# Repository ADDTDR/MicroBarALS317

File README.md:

# ALS317 Bar graph display
## Based on is31fl3730 i2c led driver and ALS317 5 segment led display

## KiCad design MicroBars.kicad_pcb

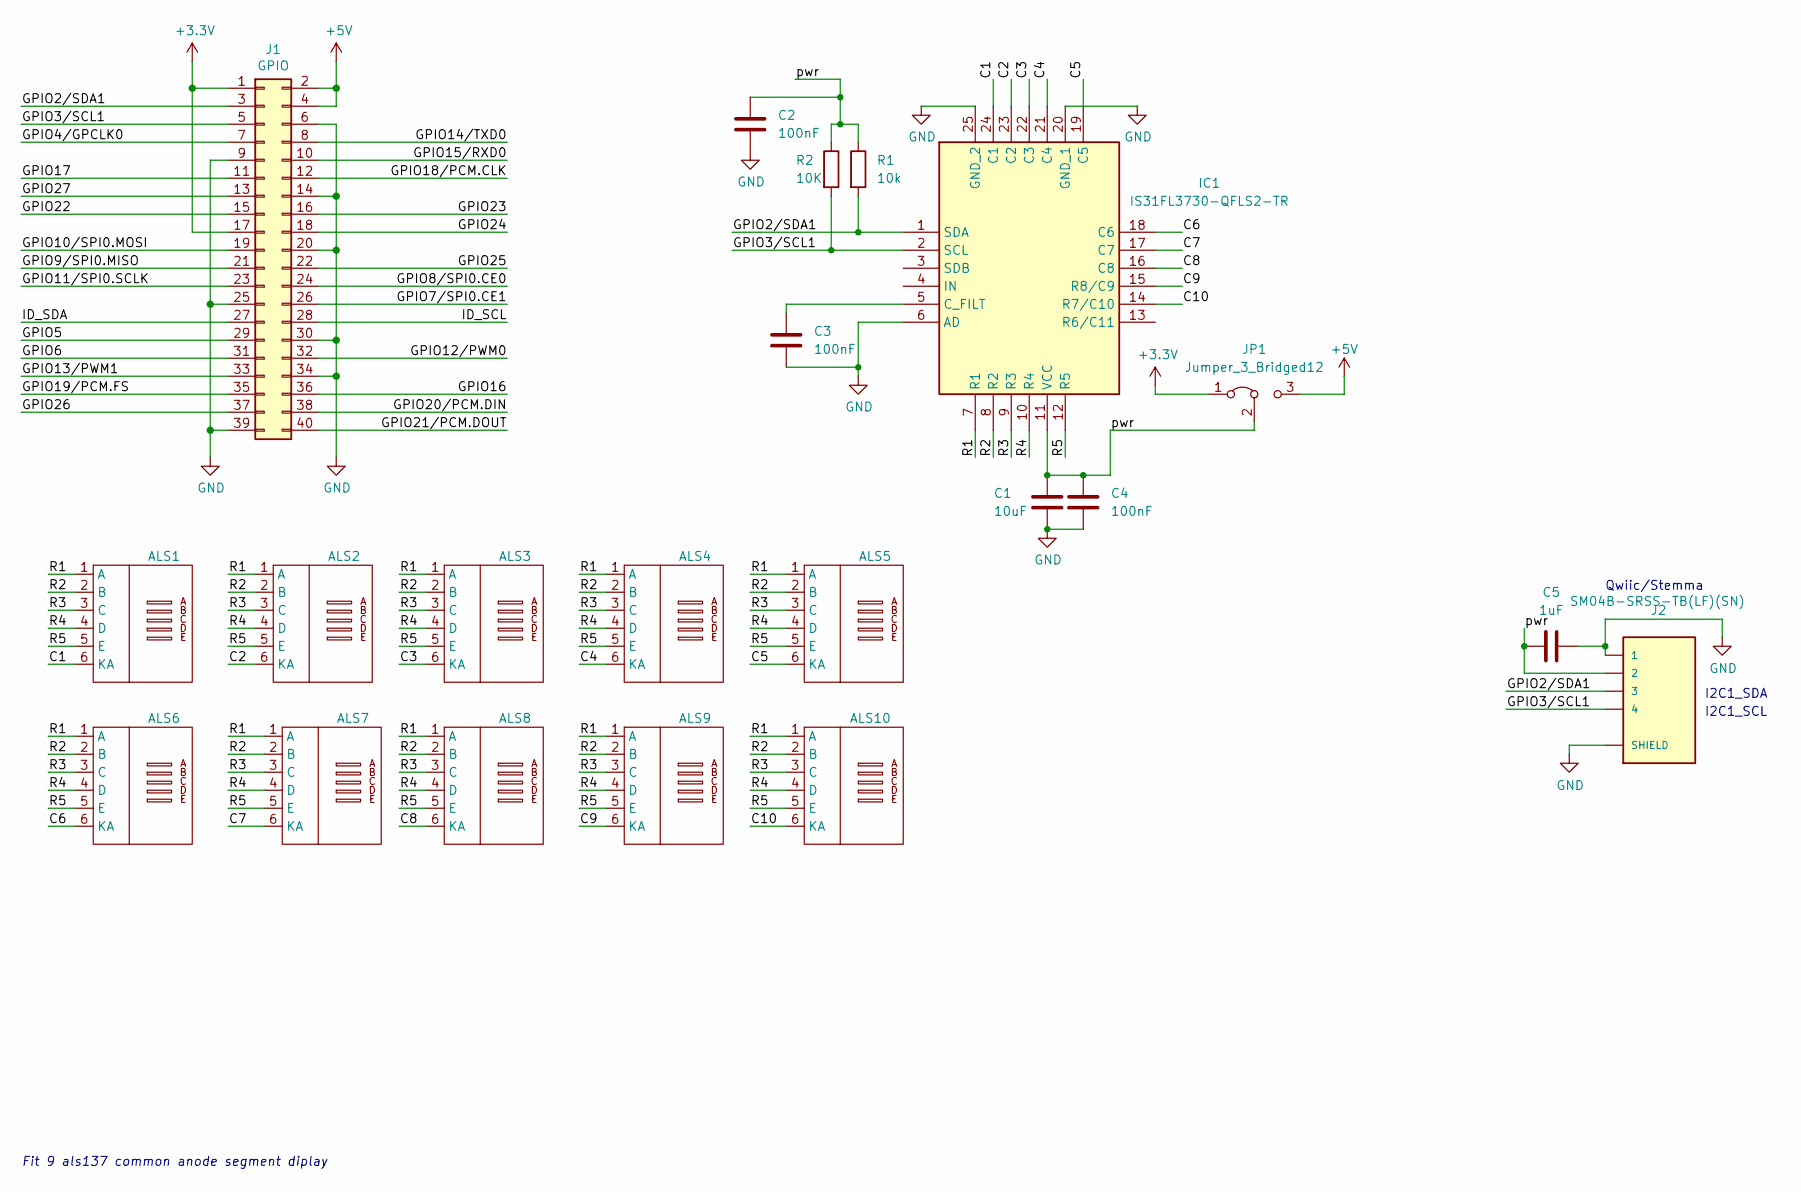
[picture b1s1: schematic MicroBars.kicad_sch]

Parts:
ALS1, ALS2, ALS3, ALS4, ALS5, ALS6, ALS7, ALS8, ALS9, ALS10: als317
C1: 10uF; C_0805_2012Metric
C2, C3, C4: 100nF; C_0603_1608Metric_Pad1.08x0.95mm_HandSolder
C5: 1uF; C_1210_3225Metric_Pad1.33x2.70mm_HandSolder
IC1: IS31FL3730-QFLS2-TR; QFN50P400X400X80-25N-D; Manufacturer_Part_Number IS31FL3730-QFLS2-TR; Mouser Part Number 870-IS31FL3730QFLS2R
J1: GPIO; PinSocket_2x20_P2.54mm_Vertical
J2: SM04B-SRSS-TB(LF)(SN); JST_SM04B-SRSS-TB(LF)(SN); MPN SM04B-SRSS-TB(LF)(SN); Digi-Key_PN 455-1804-1-ND
JP1: Jumper_3_Bridged12; SolderJumper-3_P1.3mm_Bridged12_Pad1.0x1.5mm
R1: 10k; R_0603_1608Metric_Pad0.98x0.95mm_HandSolder
R2: 10K; R_0603_1608Metric_Pad0.98x0.95mm_HandSolder

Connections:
+3V3: J1.1, J1.17, JP1.1 (A); also elsewhere on the board
+5V: J1.2, J1.4, JP1.3 (B); also elsewhere on the board
/C1: ALS1.6 (KA), IC1.24 (C1)
/C2: ALS2.6 (KA), IC1.23 (C2)
/C3: ALS3.6 (KA), IC1.22 (C3)
/C4: ALS4.6 (KA), IC1.21 (C4)
/C5: ALS5.6 (KA), IC1.19 (C5)
/C6: ALS6.6 (KA), IC1.18 (C6)
/C7: ALS7.6 (KA), IC1.17 (C7)
/C8: ALS8.6 (KA), IC1.16 (C8)
/C9: ALS9.6 (KA), IC1.15 (R8/C9)
/C10: ALS10.6 (KA), IC1.14 (R7/C10)
/GPIO2/SDA1: IC1.1 (SDA), J1.3, J2.3, R1.2
/GPIO3/SCL1: IC1.2 (SCL), J1.5, J2.4, R2.2
/GPIO4/GPCLK0: J1.7
/GPIO5: J1.29
/GPIO6: J1.31
/GPIO7/SPI0.CE1: J1.26
/GPIO8/SPI0.CE0: J1.24
/GPIO9/SPI0.MISO: J1.21
/GPIO10/SPI0.MOSI: J1.19
/GPIO11/SPI0.SCLK: J1.23
/GPIO12/PWM0: J1.32
/GPIO13/PWM1: J1.33
/GPIO14/TXD0: J1.8
/GPIO15/RXD0: J1.10
/GPIO16: J1.36
/GPIO17: J1.11
/GPIO18/PCM.CLK: J1.12
/GPIO19/PCM.FS: J1.35
/GPIO20/PCM.DIN: J1.38
/GPIO21/PCM.DOUT: J1.40
/GPIO22: J1.15
/GPIO23: J1.16
/GPIO24: J1.18
/GPIO25: J1.22
/GPIO26: J1.37
/GPIO27: J1.13
/ID_SCL: J1.28
/ID_SDA: J1.27
/R1: ALS1.1 (A), ALS2.1 (A), ALS3.1 (A), ALS4.1 (A), ALS5.1 (A), ALS6.1 (A), ALS7.1 (A), ALS8.1 (A), ALS9.1 (A), ALS10.1 (A), IC1.7 (R1)
/R2: ALS1.2 (B), ALS2.2 (B), ALS3.2 (B), ALS4.2 (B), ALS5.2 (B), ALS6.2 (B), ALS7.2 (B), ALS8.2 (B), ALS9.2 (B), ALS10.2 (B), IC1.8 (R2)
/R3: ALS1.3 (C), ALS2.3 (C), ALS3.3 (C), ALS4.3 (C), ALS5.3 (C), ALS6.3 (C), ALS7.3 (C), ALS8.3 (C), ALS9.3 (C), ALS10.3 (C), IC1.9 (R3)
/R4: ALS1.4 (D), ALS2.4 (D), ALS3.4 (D), ALS4.4 (D), ALS5.4 (D), ALS6.4 (D), ALS7.4 (D), ALS8.4 (D), ALS9.4 (D), ALS10.4 (D), IC1.10 (R4)
/R5: ALS1.5 (E), ALS2.5 (E), ALS3.5 (E), ALS4.5 (E), ALS5.5 (E), ALS6.5 (E), ALS7.5 (E), ALS8.5 (E), ALS9.5 (E), ALS10.5 (E), IC1.12 (R5)
/pwr: C1.1, C2.1, C4.1, C5.1, IC1.11 (VCC), J2.2, R1.1, R2.1; also elsewhere on the board
GND: C1.2, C2.2, C3.2, C4.2, C5.2, IC1.6 (AD), IC1.20 (GND_1), IC1.25 (GND_2), J1.6, J1.9, J1.14, J1.20, J1.25, J1.30, J1.34, J1.39, J2.1, J2.S1 (SHIELD), J2.S2 (SHIELD)
unnamed: C3.1, IC1.5 (C_FILT)

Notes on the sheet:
Qwiic/Stemma
I2C1_SCL
Fit 9 als137 common anode segment diplay
I2C1_SDA

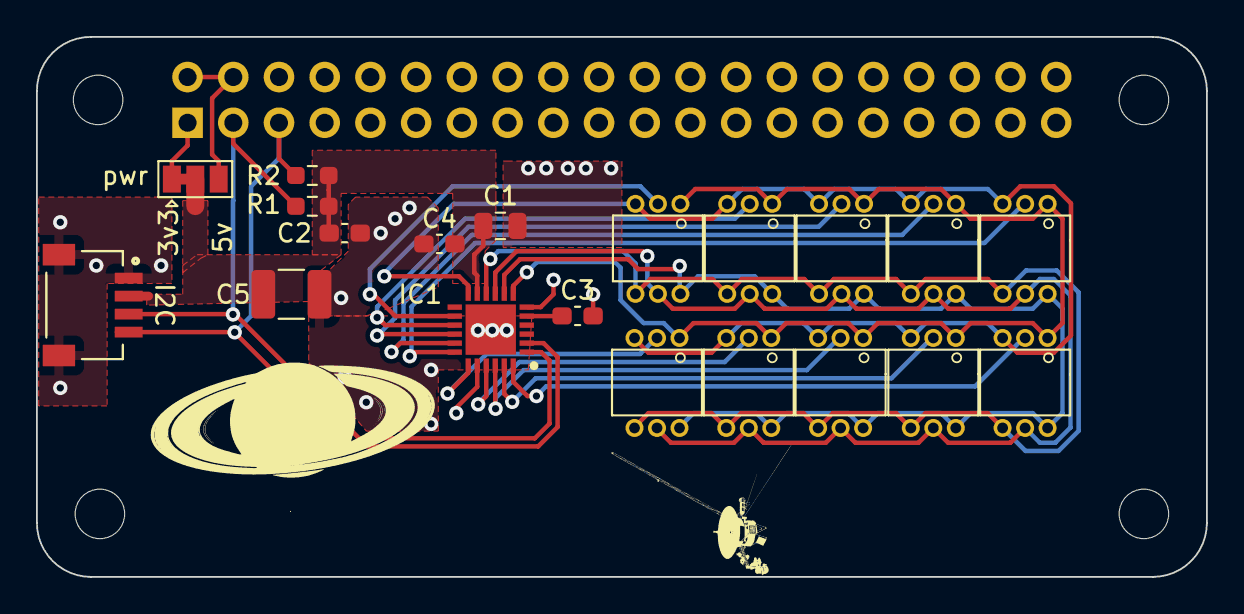
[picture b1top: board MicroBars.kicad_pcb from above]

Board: 2 copper layers, 65.0 x 30.0 mm, 21 parts (1 on the bottom side), 22 nets.

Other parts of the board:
pwr: Jumper_3_Bridged12; SolderJumper-3_P1.3mm_Bridged12_Pad1.0x1.5mm

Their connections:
+3V3: pwr.1 (A); also elsewhere on the board
+5V: pwr.3 (B); also elsewhere on the board
/pwr: pwr.2 (C); also elsewhere on the board

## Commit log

2023-11-18 Version 1
2023-11-19 Add readme
2023-11-19 Fix typo
2024-02-03 Add images of the built sample
